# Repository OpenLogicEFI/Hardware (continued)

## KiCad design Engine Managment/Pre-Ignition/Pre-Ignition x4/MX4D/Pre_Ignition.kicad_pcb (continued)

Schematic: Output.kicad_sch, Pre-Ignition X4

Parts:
A1: DRV8825; DVR8825-Labeled-Front
C38: 100nF; C_0603_1608Metric; LCSC C14663
C39: 220uf; CP_6.3x11mm_horiz-R
D4, D5, D6, D7: 1n4148ws; D_SOD-323F; LCSC C2128
JP6: SolderJumper_3_Open; SolderJumper-3-OPEN
Q5, Q6, Q7, Q8: AO3400A; SOT-23; LCSC C20917
R7, R8, R9, R10: 470r; R_0402_1005Metric; LCSC C25117
R15, R16, R17, R18, R54: 51k; R_0402_1005Metric; Manufacture Part Number 0402WGF5102TCE; LCSC C25794
R62: 10k; R_0603_1608Metric; LCSC C25804
U5: ULN2003A; SOIC-16_3.9x9.9mm_P1.27mm; LCSC C7512

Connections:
+5V: A1.13 (~RST), A1.14 (~SLP), JP6.3 (B); also elsewhere on the board
+BATT: A1.8 (VMOT), C38.2, C39.1, D4.1 (K), D5.1 (K), D6.1 (K), D7.1 (K), JP6.1 (A), U5.9 (COM); also elsewhere on the board
BOOST: D4.2 (A), Q5.3 (D); also elsewhere on the board
D39: U5.15 (O2); also elsewhere on the board
D41: U5.16 (O1); also elsewhere on the board
D53: U5.11 (O6), U5.12 (O5); also elsewhere on the board
Fan: U5.13 (O4); also elsewhere on the board
Fuel-Pump: U5.14 (O3); also elsewhere on the board
GND: A1.1 (GND), A1.7 (GND), C38.1, C39.2, Q5.2 (S), Q6.2 (S), Q7.2 (S), Q8.2 (S), R15.1, R16.1, R17.1, R18.1, R54.1, U5.8 (GND); also elsewhere on the board
IDLE: D6.2 (A), Q7.3 (D); also elsewhere on the board
IDLE2: D5.2 (A), Q6.3 (D); also elsewhere on the board
MC-D4: R10.2, R18.2; also elsewhere on the board
MC-D5: R9.2, R17.2; also elsewhere on the board
MC-D6: R8.2, R16.2; also elsewhere on the board
MC-D7: R7.2, R15.2; also elsewhere on the board
MC-D16: A1.16 (DIR); also elsewhere on the board
MC-D17: A1.15 (STEP); also elsewhere on the board
MC-D24: A1.9 (~EN); also elsewhere on the board
MC-D39: U5.2 (I2); also elsewhere on the board
MC-D41: U5.1 (I1); also elsewhere on the board
MC-D45: U5.3 (I3); also elsewhere on the board
MC-D47: U5.4 (I4); also elsewhere on the board
MC-D49: R54.2, U5.7 (I7); also elsewhere on the board
MC-D53: U5.5 (I5), U5.6 (I6); also elsewhere on the board
unnamed: JP6.2 (C), R62.2
unnamed: Q5.1 (G), R7.1
unnamed: Q6.1 (G), R8.1
unnamed: Q7.1 (G), R9.1
unnamed: Q8.1 (G), R10.1
Step-A1: A1.4 (A1); also elsewhere on the board
Step-A2: A1.3 (A2); also elsewhere on the board
Step-B1: A1.5 (B1); also elsewhere on the board
Step-B2: A1.6 (B2); also elsewhere on the board
Tach: R62.1, U5.10 (O7); also elsewhere on the board
VVT: D7.2 (A), Q8.3 (D); also elsewhere on the board

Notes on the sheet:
High Current Output - 1A Max
HC2
HC1
Relay Control Tach Output
Stepper Driver

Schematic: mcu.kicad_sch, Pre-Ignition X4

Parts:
C4, C11, C18, C25: 100nF; C_0603_1608Metric; LCSC C14663
D21: 1n4148ws; D_SOD-323F; LCSC C2128
R52: 10k; R_0603_1608Metric; LCSC C25804
R61: 470r; R_0402_1005Metric; LCSC C25117
S0: RST CTRL; 1x02-Proto
XA1: Arduino_Mega2560_Shield-Arduino; Arduino-Mega2560-Shield-Speeduino

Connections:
+3V3: XA1.3V3 (3.3V)
+5V: C4.1, C11.2, C18.2, C25.1, D21.1 (K), R52.1, R61.2, XA1.5V1 (5V), XA1.5V3 (5V), XA1.5V4 (5V); also elsewhere on the board
GND: C4.2, C11.1, C18.1, C25.2, XA1.GND1 (GND), XA1.GND2 (GND), XA1.GND3 (GND), XA1.GND5 (GND), XA1.GND6 (GND); also elsewhere on the board
MC-A0: XA1.A0; also elsewhere on the board
MC-A1: XA1.A1; also elsewhere on the board
MC-A2: XA1.A2; also elsewhere on the board
MC-A3: XA1.A3; also elsewhere on the board
MC-A4: XA1.A4; also elsewhere on the board
MC-A5: XA1.A5; also elsewhere on the board
MC-A6: XA1.A6
MC-A7: XA1.A7
MC-A8: XA1.A8; also elsewhere on the board
MC-A9: XA1.A9; also elsewhere on the board
MC-A10: XA1.A10; also elsewhere on the board
MC-A11: XA1.A11
MC-A12: XA1.A12
MC-A13: XA1.A13
MC-A14: XA1.A14
MC-A15: XA1.A15
MC-AREF: XA1.AREF
MC-D0-RX: XA1.D0 (D0_RX0); also elsewhere on the board
MC-D1-TX: XA1.D1 (D1_TX0); also elsewhere on the board
MC-D2: XA1.D2 (D2_INT0); also elsewhere on the board
MC-D3: XA1.D3 (D3_INT1)
MC-D4: XA1.D4; also elsewhere on the board
MC-D5: XA1.D5; also elsewhere on the board
MC-D6: XA1.D6; also elsewhere on the board
MC-D7: XA1.D7; also elsewhere on the board
MC-D8: XA1.D8; also elsewhere on the board
MC-D9: XA1.D9; also elsewhere on the board
MC-D10: XA1.D10; also elsewhere on the board
MC-D11: XA1.D11; also elsewhere on the board
MC-D12: XA1.D12
MC-D13: XA1.D13
MC-D14-TX: XA1.D14 (D14_TX3); also elsewhere on the board
MC-D15-RX: XA1.D15 (D15_RX3); also elsewhere on the board
MC-D16: XA1.D16 (D16_TX2); also elsewhere on the board
MC-D17: XA1.D17 (D17_RX2); also elsewhere on the board
MC-D18: XA1.D18 (D18_TX1); also elsewhere on the board
MC-D19: XA1.D19 (D19_RX1); also elsewhere on the board
MC-D20: XA1.D20 (D20_SDA); also elsewhere on the board
MC-D21: XA1.D21 (D21_SCL)
MC-D22: XA1.D22
MC-D23: XA1.D23
MC-D24: XA1.D24; also elsewhere on the board
MC-D25: XA1.D25
MC-D26: XA1.D26
MC-D27: XA1.D27
MC-D28: XA1.D28
MC-D29: XA1.D29
MC-D30: XA1.D30
MC-D31: XA1.D31
MC-D32: XA1.D32
MC-D33: XA1.D33
MC-D34: XA1.D34
MC-D35: XA1.D35
MC-D36: XA1.D36
MC-D37: XA1.D37
MC-D38: XA1.D38; also elsewhere on the board
MC-D39: XA1.D39; also elsewhere on the board
MC-D40: XA1.D40; also elsewhere on the board
MC-D41: XA1.D41; also elsewhere on the board
MC-D42: XA1.D42
MC-D43: XA1.D43
MC-D44: XA1.D44
MC-D45: XA1.D45; also elsewhere on the board
MC-D46: XA1.D46
MC-D47: XA1.D47; also elsewhere on the board
MC-D48: XA1.D48
MC-D49: XA1.D49; also elsewhere on the board
MC-D50: XA1.D50; also elsewhere on the board
MC-D51: XA1.D51; also elsewhere on the board
MC-D52: XA1.D52; also elsewhere on the board
MC-D53: XA1.D53 (D53_SS); also elsewhere on the board
MC-IOREF: XA1.IORF (IOREF)
MC-RESET: D21.2 (A), R52.2, S0.1, XA1.RST1 (RESET)
MC-SCL: XA1.SCL
MC-SDA: XA1.SDA
unnamed: R61.1, S0.2

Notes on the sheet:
Remove DC Jack for proper fitment.
Reset Control
Scattered decoupling
S1 Reference used to match 0.4x schematic
MCU
Arduino Mega 2560 R3

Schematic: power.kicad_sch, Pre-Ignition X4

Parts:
C1: 33uF; CP_EIA-7343-31_Kemet-D; LCSC C571271
C2: 2.2uF; C_1206_3216Metric; Manufacture Part Number CL31B225KBHNNNE; LCSC C50254
C3: 330nF; C_0805_2012Metric; Manufacture Part Number 0805B334K500NT; LCSC C1740
C5, C13: 100nF; C_0603_1608Metric; LCSC C14663
C6: 10uF; CP_EIA-3216-18_Kemet-A; Manufacture Part Number TAJA106K016RNJ; LCSC C7171
C12: 1uF; C_0603_1608Metric; LCSC C15849
D1: SS14; D_SMA; Manufacture Part Number SS14; LCSC C2480
D2: SMAJ18CA; D_SMA; Manufacture Part Number SMAJ18CA; LCSC C19077539
D3: SMF6.0CA; D_SOD-123F; LCSC C2990473
D17, D18: LED; LED_0603_1608Metric; LCSC C2286
IC1: L78M05ABDT-TR; TO-252-2-Thermal-with-Silk; Manufacture Part Number L78M05ABDT-TR; LCSC C58069
R22: 1k; R_0402_1005Metric; Manufacture Part Number 0402WGF1001TCE; LCSC C11702
R23: 0r; R_1206_3216Metric; LCSC C17888
R24: 2.4k; C_0603_1608Metric; LCSC C22940

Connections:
+5V: C5.2, C6.1, D3.1 (A1), IC1.3 (OUT), R23.2; also elsewhere on the board
+5VA: C12.1, C13.2, R22.1, R23.1; also elsewhere on the board
+BATT: D1.2 (A), D2.2 (A2), R24.2; also elsewhere on the board
GND: C1.2, C2.2, C3.2, C5.1, C6.2, C12.2, C13.1, D2.1 (A1), D3.2 (A2), D17.1 (K), D18.1 (K), IC1.2 (GND); also elsewhere on the board
unnamed: C1.1, C2.1, C3.1, D1.1 (K), IC1.1 (IN)
unnamed: D17.2 (A), R22.2
unnamed: D18.2 (A), R24.1

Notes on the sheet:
Primary Power input
External 5v Reference.
Power Supply

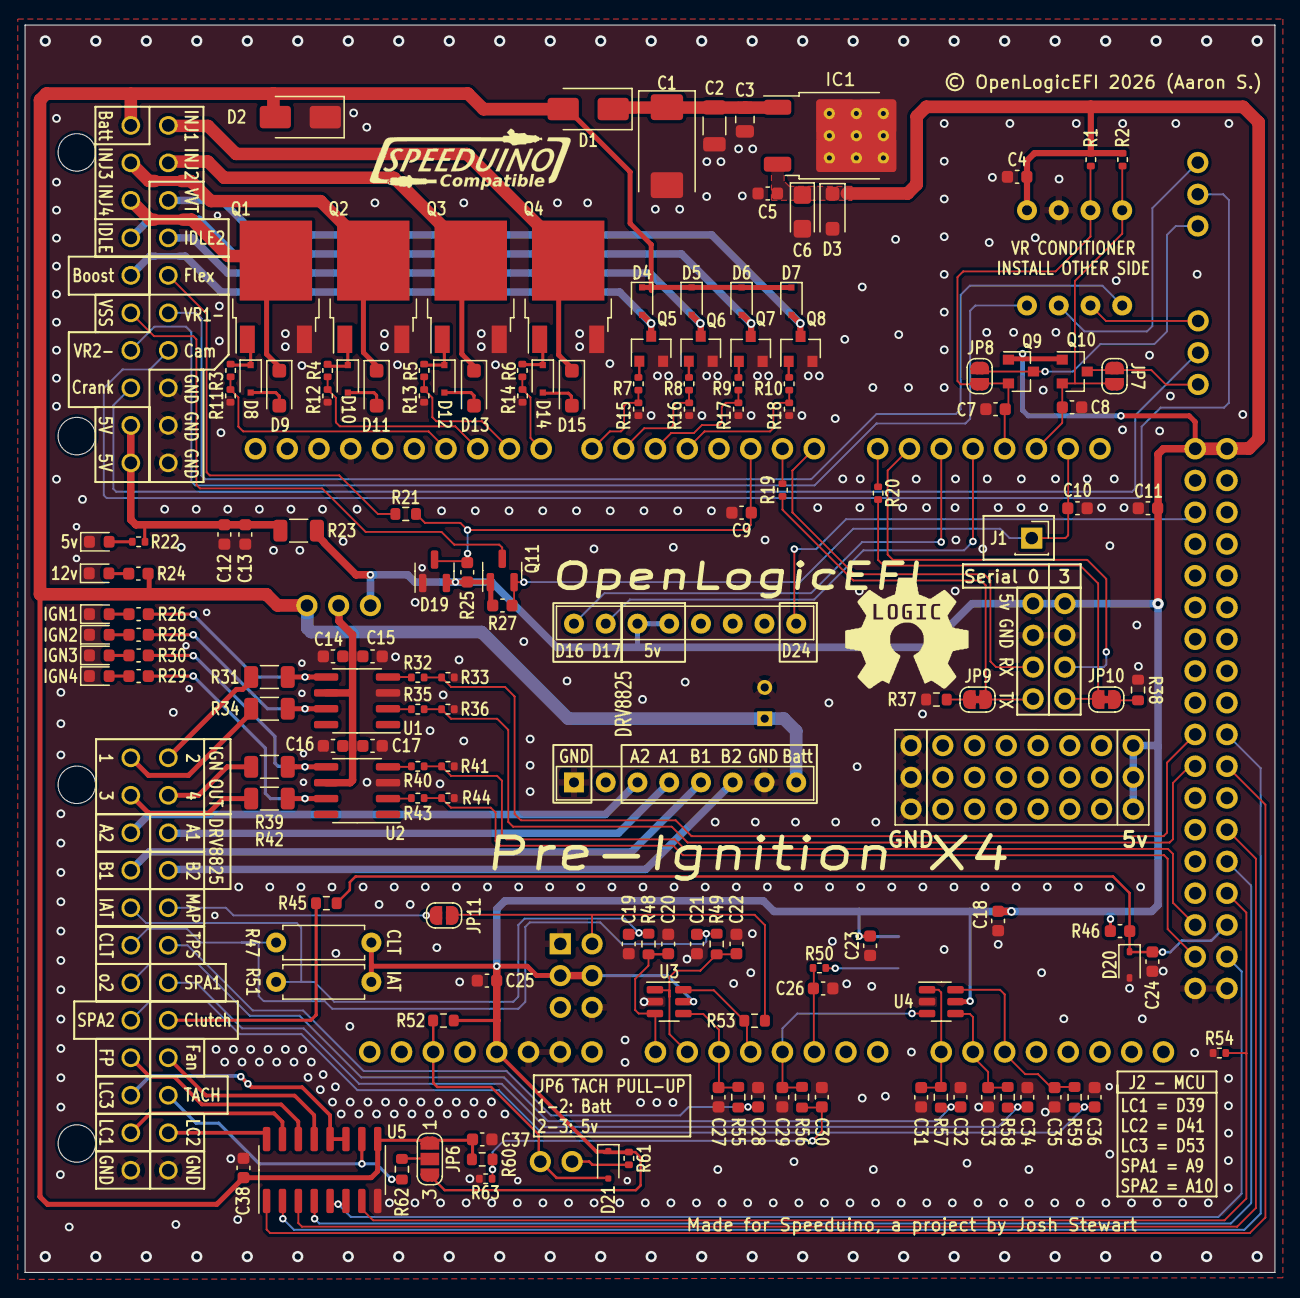
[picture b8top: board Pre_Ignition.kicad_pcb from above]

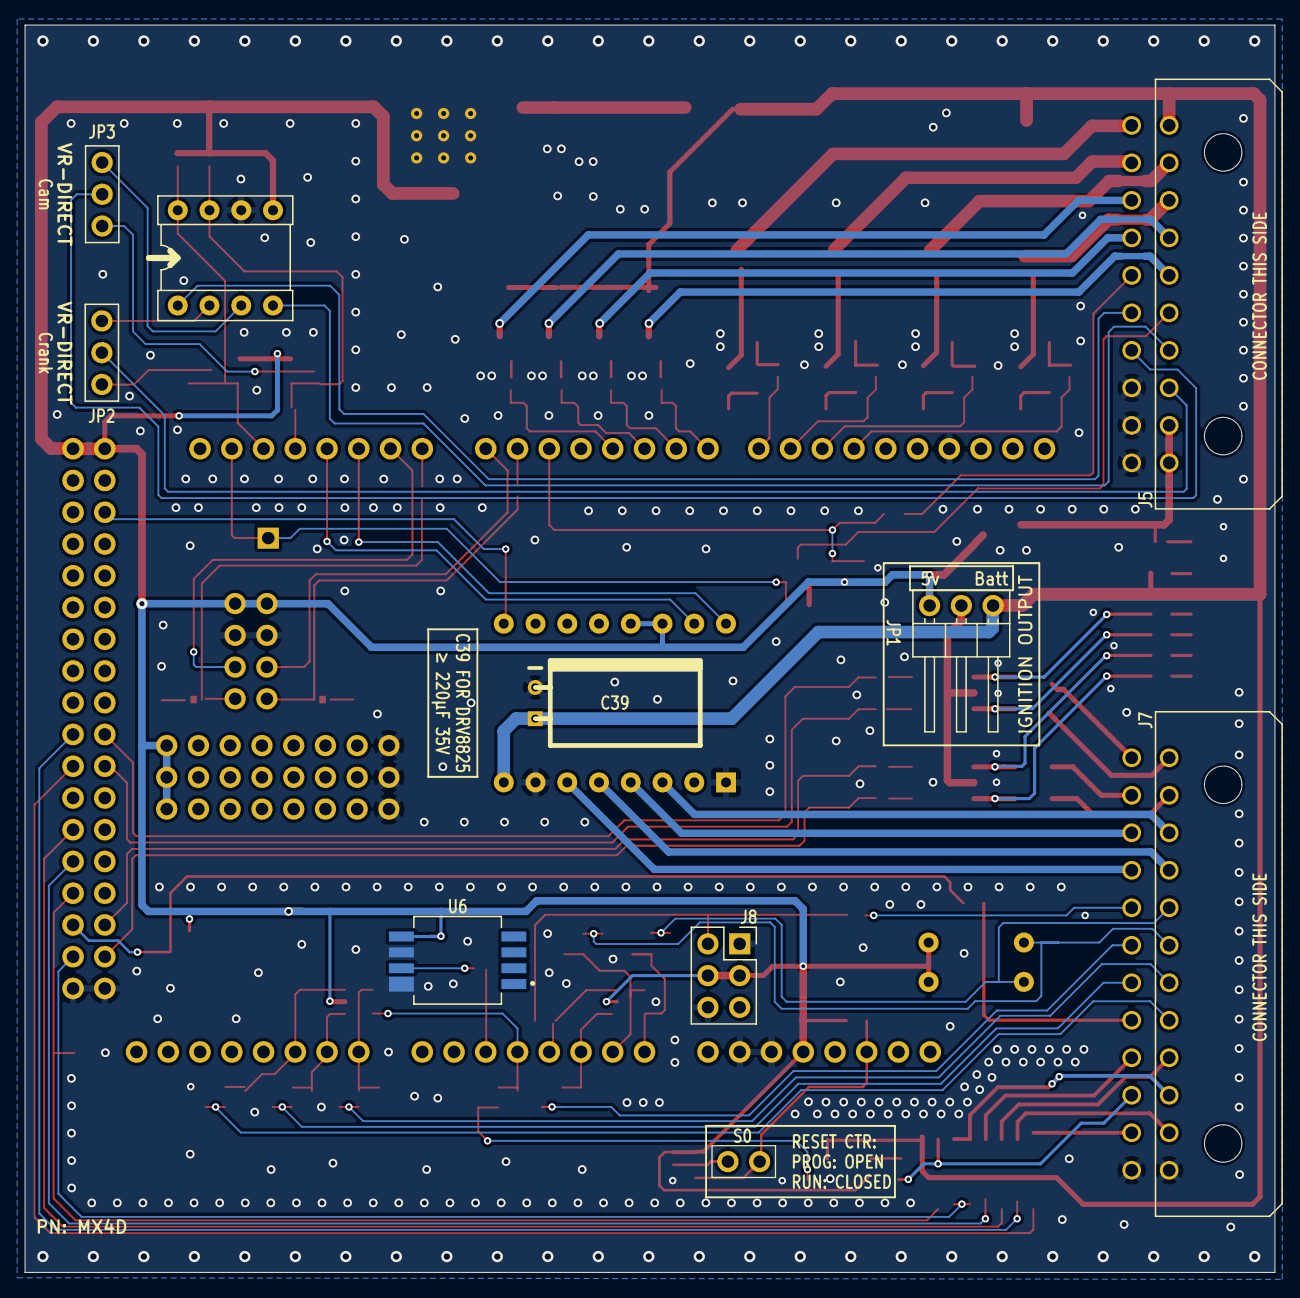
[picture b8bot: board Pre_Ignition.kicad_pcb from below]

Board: 2 copper layers, 100.0 x 99.8 mm, 166 parts (10 on the bottom side), 121 nets.

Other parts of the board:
G1: LOGO; SpeeduinoCompatible-17mm
G2: LOGO; open-logic-10

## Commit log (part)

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2021-08-05 schematic upload for 1.3
    PDF
2021-08-11 Release of Pre-Ignition X4
    Initial upload of Pre-Ignition X4
2021-09-18 Folder Organization
2021-09-21 Initial Upload of DetonationEMS 1.3 Rev E
    Latest version of 1.3 brings several new features and an easier to use layout.
2021-09-21 Pre-Ignition x4 MX4B upload for reference only
2021-09-22 Pre-Ignition x2 Initial Upload, MX4B Production.
    Pre-Ignition x2 Initial Upload - 2 Channel Speeduino compatible ECU
    Pre-Ignition x4 MX4B (revision B) - minor updates, BOM changes, connectors moved to bottom side of board.
2021-09-22 STL update
    Added end caps for Pre-Ignition x4
    1.3 End cap updated
2021-09-22 bom fix
2021-09-23 Pinout Documentation for MX4B Updated.
    Unnecessary build files removed.
2021-09-23 MX2A Pinout Upload
    Remove unnecessary build files.
2021-09-23 x4 stl file improvments
2021-09-24 Pre-Ignition x4 pinout update
    Update pinout charts to include both top and bottom mount located connectors.
2021-10-03 update STL files
    Add Pre-ignition x2
2021-10-03 Initial Upload of VR Conditioner NCV1124
    Rename Josh's Conditioner folder and create readme.
2021-10-05 add schem PDF
    added PDF schematic for x2
2021-10-09 DetoStim initial Upload
    DetoStim initial Upload - Engine Simulator for Ardustim
    Update a few readme files.
2022-02-17 VR Conditioner Update
    Update Schematic
    Include Instructions
    Update Readme
2022-02-17 DetoStim Upload
    Product read upload
2022-02-17 Delete Simulator-2022-02-17_154741.zip
    remove kicad backup
2022-03-15 Pre-Ignition X2 Harness
    Color coded diagram
2022-03-23 x4 harness
2022-07-17 Update readme.md
    Organizing links and information to easier understand.
    Add website shield.io
    Add TAPR license link
    Add Support page link
2022-08-21 Rename Readme.txt to Readme.md
2022-08-21 8channel Simulator and re-organize
    Initial Upload - 8 Channel Engine Simulator
    File structure organize.
2022-08-21 Place holders
2022-09-11 Minor Corrections
    Silkscreen Correction - Cam and Crank output labels were swapped
    Output pulse LED's removed (Serve no purpose)
    Minor layout improvements.
2022-10-29 Schematic Correction
    VRConditioner NCV1124 schematic math correction.
    Readme Updated for upcoming revision
    Instructions Added to RevA folder
2022-11-07 Remove unnecessary pinout
    Remove top mount pinout from MX4B. It was only used of a select few MX4A
2022-11-17 Product upload, file organization.
    Initial upload of NCV1124 based condition RevB
    File organization, removal of unnecessary files.
2022-11-17 Engine Simulator RevB Initial upload
    Improved design 8 Channel engine simulator. Optocoupler output allows for more versatile signal output usage.
    Fixed silk screen error.
2022-11-30 Update README.md
    spelling mistake
2022-12-11 File organization.
    Remove redundant files.
2022-12-27 MX4B-2 initial upload. MX4X Pinout
    Pre-ignition MX4B-2 Initial upload
    Pinout documentation clarification updated.
2022-12-27 MX4C Initial Upload
2023-03-24 EngineSim PCB rev-c, minor fixed/layout changes.
    see readme
2023-05-11 Upload correct initial upload files
    Initial upload files were accidently taken from an alpha folder. 5v pins on main connector had no voltage. To fix the issue on any manufactured boards remove C8 and C9. Then short the pins of the rem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
2023-06-14 VRNCV-B
    Layout update. Schematic unchanged.
2023-06-14 Engine Simulator Upload Revision Correcton
    Minor changes were made to RevB and uploaded as RevC by mistake. RevB minor layout changes for ease of use. Protection Zener added. Label correction.
2023-06-15 Structure Update
    MX2 - RevB Upload
    MX4B-2 - KiCad Version update (no changes)
    MX4C - Organized Schematic, Minor layout change
    Engine Simulator 8 Channel - Organized Schematic (no changes)
    PMAP-M - Map Sensor Breakout for MX4C
2023-09-07 organization of pinouts
    Organization of pinout documents for easy linking to detonationems.com
2023-10-24 minor update
    Copper Pour and clearances updated.
2023-10-27 MX4C PCB end caps
    Initial upload of Pre-Ignition x4 MX4C PCB end caps
2023-12-25 Update README.md
    rebrand - website remains for now
2024-01-01 Readme update
2024-01-01 Update README.md
    Migration
2024-01-13 Initial upload PMAP-M
    Updated map sensor design for OpenLogicEFI ECU's.
    SHOULD NOT BE USED FOR BOARDS LABLED "DETONATIONEMS".
2024-02-08 Minor updates
    PMAP-M correction
    Endcap updates
    readme updates
2024-05-24 Update README.md
    correct support link
2024-07-06 Closed-Deck-x4
    Initial hardware upload
2024-07-17 Initial upload spark gap x4
2024-08-05 spark-gap pinout correction
    Fix numeral mistake on SGx4 pinout pdf
    upload B&W version
2024-10-08 Initial upload NCV1124 RevB2
    NVC1124 RevB2 upload
    Ncv1124 RevB - spelling correction
2024-10-08 schematic exports
    kicad version updates, schematic exports
2025-04-27 minor document changes
    CD pinout zip
2025-04-27 pre-ignition documentation reorganize
2025-05-05 file relocation
    schematic relocation
2025-05-19 CDx4a RevA3 | Engine Sim RevB2: initial upload
    CDx4 RevA3: Minor layout changes, improved protection and stability, PCB edgecut corrections
    Engine Sim RevB2: Minor layout changes, added additional protection.
2025-05-19 pmap-m update
    bom update (footprint change)
2025-05-19 Spark Gap X4 RevC
    RevC initial upload
    Note: RevB was never released.
2025-05-19 ICM2a Initial Upload
2025-05-19 VRMAX-B initial upload
    Very minor changes:
    Slight footprint location changes
    Minor slikscreen changes.
2025-05-19 Repair file structure
    Remove redundant hardware/hardware folder
2025-05-20 icm-2 install PDF
2025-05-30 document organization
    document organization
    mx4c & sim8-b2 schematic PDF upload
2025-05-30 fix the fix (oops)
    fix mistakes in schematic location file structure..
2026-03-03 mx4d initial upload
    MX4D comes with quality, layout, protection and IC
2026-06-21 Reorganization - Version uploads
    CDx4 B1,2 - NCV1124 B3 - PMAPM 2 - Sim8 B3 - Upload
    Remove ICM2A (design issues), Upload ICM2B Major redesign,
2026-06-21 INJ N-fet upload - Date corrections
    N-Fet Initial Upload, recent upload date corrections.
